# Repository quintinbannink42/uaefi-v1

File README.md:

# Ultra Affordable EFI

🟢[$175 base model rusEFI store](https://www.shop.rusefi.com/shop/p/uaefi-ultra-affordable-efi)🟢

## Community Support

🔴Community support ONLY 🔴 https://www.facebook.com/groups/rusEfi 🔴 [Discord](https://github.com/rusefi/rusefi/wiki/Discord)🔴

## SUPERSEAL 60 harness (fork)

This fork uses one TE SUPERSEAL 1.0 60-position header, **6437288-5**, on the left edge (J30 at 28.2, 138, rotation 90°, pin 1 at the south end). The dual AMPSEAL 35 headers and the 2.54 mm 2×02 sockets are removed. Ignition is logic-level smart coils only; the onboard ISL9V3040 IGBTs Q7–Q12 stay off the board. Outline is 125 × 100 mm (x 25–150, y 60–160). The old socket pin-name legend is gone; J30 keeps a silkscreen “1” on pin 1. See [docs/superseal-60-pinout.md](docs/superseal-60-pinout.md) and [docs/superseal-60-order.md](docs/superseal-60-order.md).

## Technical Details

Open Source KiCAD 7 hardware powered by [Hellen-One](https://github.com/andreika-git/hellen-one)

powerted by [rusEFI firmware](https://github.com/rusefi/rusefi)

[User Documentation](https://github.com/rusefi/rusefi/wiki/uaEFI)

## MCU options

1mg of flash is _required_.

One day we shall try https://jlcpcb.com/partdetail/Stmicroelectronics-STM32F427VIT6%2FC57097#EC or https://jlcpcb.com/partdetail/Stmicroelectronics-STM32F437VIT7%2FC1338578#EC

## rusEFI Store

https://www.shop.rusefi.com/shop/p/uaefi-ultra-affordable-efi

## HOWTO JLCPCB

You would need three files from ``boards/uaefi-a/board`` folder to place your JLCPB Assembly order: gerber.zip BOM-JLC.csv and CPL.csv

### Q: Something wrong with BOM?

A: Nope, that's normal nothing to worry about click 'Continue'.

### Q: how do I get more RAM for Lua?

A: fabricate with STM32F42xVI firmware would defect extra RAM and give you extra Lua. Once your script does not fit into STM32F42xVI it's F7 time or help us leverage F413.

### Q: I've place an order with JLCPCB and I see scary looking wrong orientation?

A: that's expected. See [boards/uaefi-c/board](boards/uaefi-c/board) ``Original*.png`` files and ``Produce*.png`` after JLCPCB manual review process.

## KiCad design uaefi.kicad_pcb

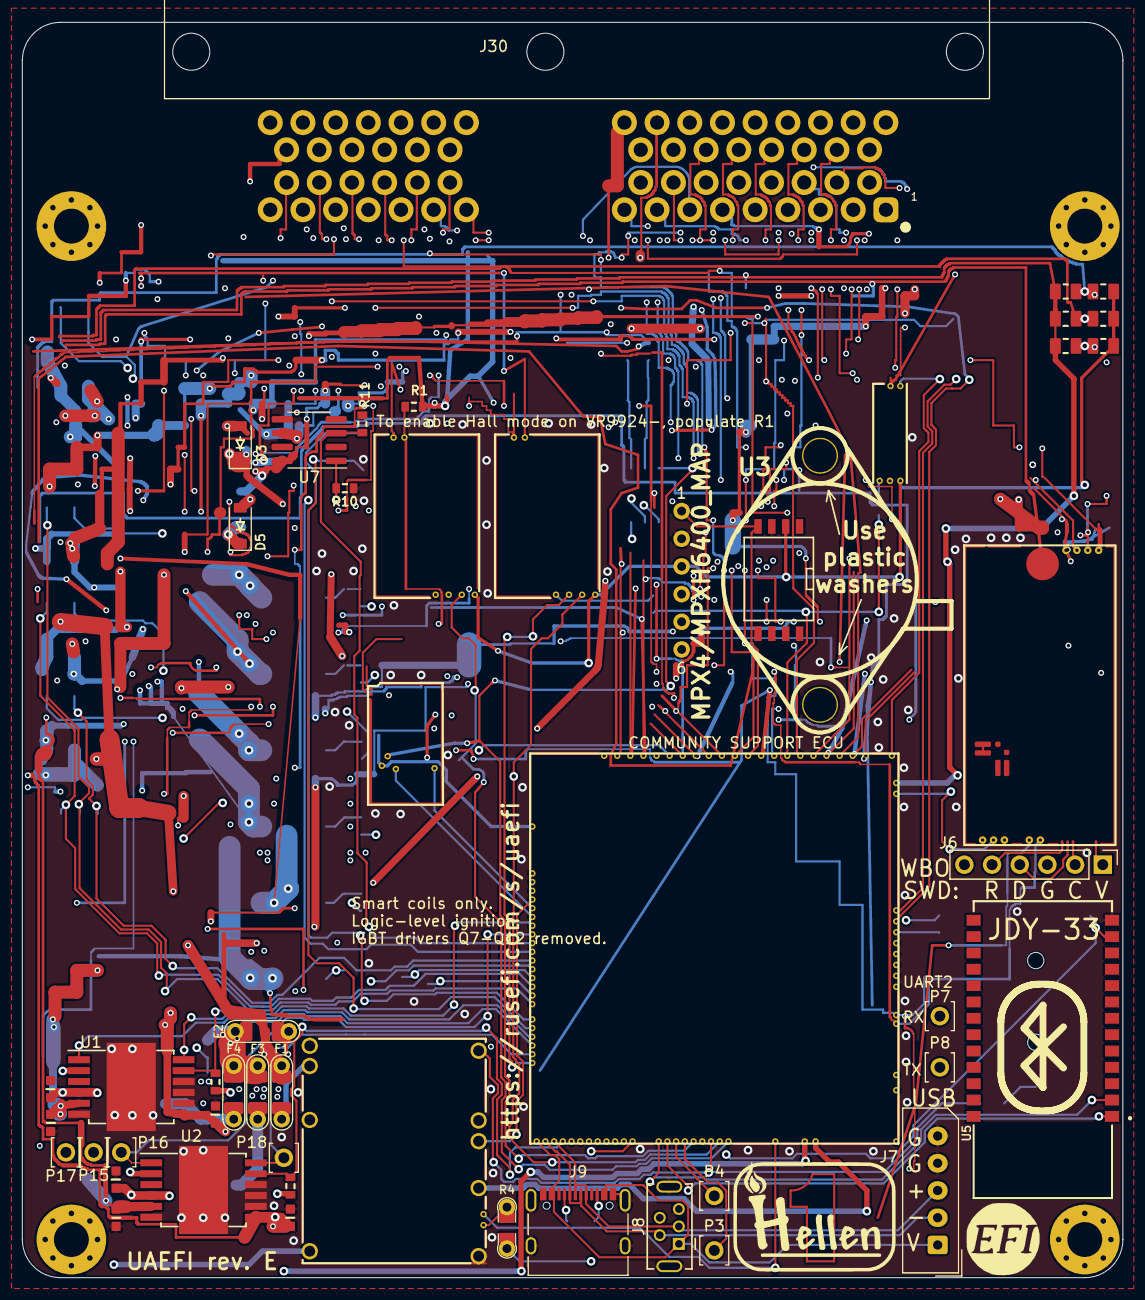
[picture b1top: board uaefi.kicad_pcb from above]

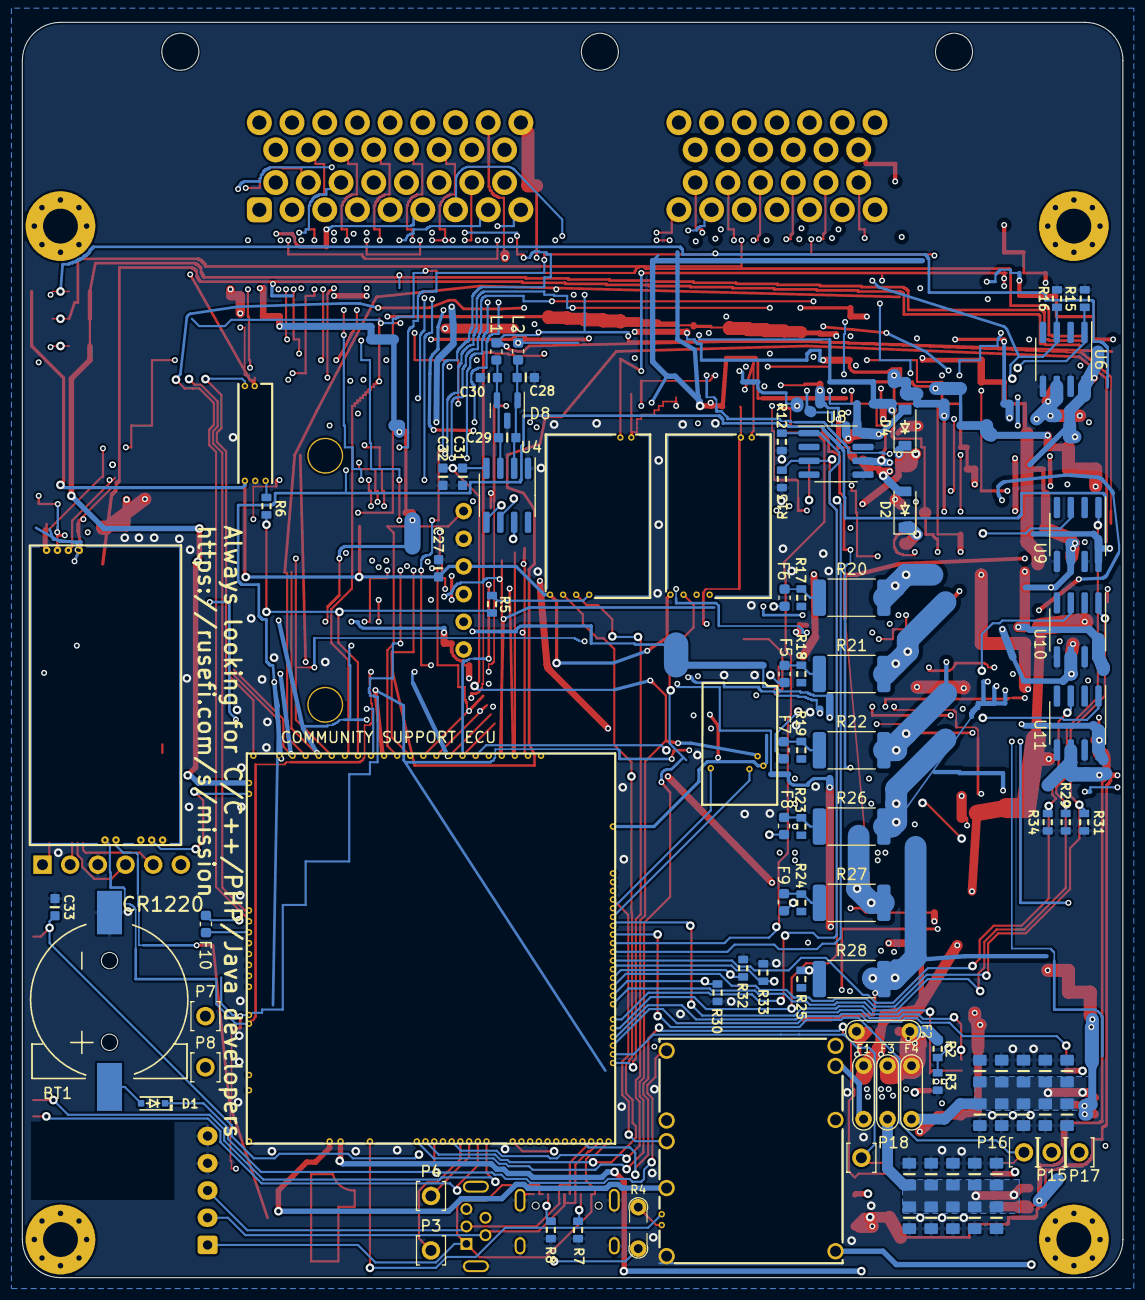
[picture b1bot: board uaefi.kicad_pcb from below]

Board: 4 copper layers, 101.0 x 115.2 mm, 129 parts (74 on the bottom side), 132 nets.

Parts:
BT1: CR1220; CR1220-2
C1, C2, C3, C4, C5, C6, C7, C8, C9, C10, C14, C15, C16, C17, C18, C19, C20, C21, C22, C23: 10u; C0805
C11, C24, C27, C29, C31, C33: 100n; C0603
C12, C13, C25, C26, C28, C30: 10n; C0603
C32: 1u; C0603
D1: 1N4148WS; SOD-323
D2, D3, D4, D5: B5819W; SOD-123
D8: NUP2105L; SOT-23
F1, F2, F3, F4: 12H1500D; PAD-1206-PAD
F5, F6, F7, F8, F9, F10: 50mA; Fuse_0603_1608Metric
G1: RUSEFI_LOGO; rusefi_logo
G2: LOGO
H1, H2, H3, H4: M3; MountingHole_3.2mm_M3_Pad_Via
J6: Conn_01x06; PinHeader_1x06_P2.54mm_Vertical
J7: Conn_01x05_Male; Molex_SPOX_5267-05A_1x05_P2.50mm_Vertical
J8: USB_B_Mini; USB-MINI-B-VERTICAL
J9: USB_C
J30: 6437288-5; TE_6437288-5_SuperSeal_60_RA
L1, L2: 470R@100MHz; L_0603_1608Metric
M1: Module-power_12and5V-0.3; power_12and5V
M2: Module-knock-0.2; knock
M3: Module-vr-discrete-0.5; vr-discrete
M4: Module-vr-max9924-0.1; vr-max9924
M5: Module-wbo-0.5; wbo
M6: Module:mega-mcu100/0.3; mega-mcu100
M7: Module-can-0.1; can
P3, P4, P7, P8, P15, P16, P17, P18: Pad; PAD-TH
R1, R9, R10, R11, R12, R13, R14, R15, R16, R29, R30, R31, R32, R33, R34: 4.7k; R0603
R2: 33k; R0603
R3: 6.8k; R0603
R4: Jumper-Pad-Pad; PAD-0805-PAD
R5, R6: 0; R0603
R7, R8: 5.6k; R0603
R17, R18, R19, R23, R24, R25: 22; R0603
R20, R21, R22, R26, R27, R28: 0; R_2512_6332Metric
R35, R36, R37: 10k; R0805
R38, R39, R40: DNP; R0805
U1, U2: TLE9201SG; Infineon_PG-DSO-12-11
U3: MPX4/MPXH6400_MAP; MPX-4_MAP
U4: MAX31855KASA; SOIC-8_3.9x4.9mm_P1.27mm
U5: JDY-33
U6, U7, U8, U9, U10, U11: VNLD5160TR-E; SOIC-8_3.9x4.9mm_P1.27mm

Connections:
+3.3V: M6.N21 (V33), R9.2, R14.2, U1.2 (VSO), U2.2 (VSO)
+3.3VA: C31.2, C32.2, C33.2, M6.N15 (V33_SWITCHABLE), M7.V2 (CAN_VIO), U4.4 (V_CC), U5.12 (3V3)
+5V: M1.E4 (V5), M6.N22 (VCC)
+5VA: C27.2, M2.E1 (V5A), M3.E4 (V5_IN), M4.E4 (V5_IN), M5.W1 (V5_IN), M6.E1 (V5A_SWITCHABLE), M6.W2 (V5A_SWITCHABLE), M7.V1 (V5), R38.2, R39.2, R40.2, U3.3 (VCC)
+5VP: J30.7, M1.V4 (5VP), R1.1
+12V: F2.1, F3.1, F4.1, J30.1, R2.2
+12V_RAW: D2.1 (K), D3.1 (K), D4.1 (K), D5.1 (K), F2.2, J30.2, M1.V1 (V12_PERM), M1.V3 (V12_RAW)
/12V_KEY: F1.1, J30.3
/ADC3: M6.S15 (IN_KNOCK_(PA2)), R5.2, R6.2
/CAN+: J30.9, M5.W4 (CANH), M6.W11 (CANH)
/CAN-: J30.35, M5.W3 (CANL), M6.W12 (CANL)
/DC1_DIR: M6.E21 (OUT_PWM4_(PC8)), P15.1, U1.1 (DIR)
/DC1_DIS: M6.E8 (SPI2_MISO_(PB14)), R9.1, U1.11 (DIS)
/DC1_PWM: M6.E20 (OUT_PWM3_(PC7)), P17.1, U1.12 (PWM)
/DC2_DIR: M6.E9 (SPI2_MOSI_(PB15)), P16.1, U2.1 (DIR)
/DC2_DIS: M6.N4 (USBID_(PA10)), R14.1, U2.11 (DIS)
/DC2_PWM: M6.E22 (OUT_PWM5_(PC9)), P18.1, U2.12 (PWM)
/DC Driver 1/PWR: C1.2, C2.2, C3.2, C4.2, C5.2, C6.2, C7.2, C8.2, C9.2, C10.2, C11.2, F4.2, U1.4 (VS)
/DC Driver 2/PWR: C14.2, C15.2, C16.2, C17.2, C18.2, C19.2, C20.2, C21.2, C22.2, C23.2, C24.2, F3.2, U2.4 (VS)
/EGT+: J30.36, L1.1
/EGT-: J30.37, L2.1
/EGT/SPI_CS: M6.N9 (SPI3_CS_(PA15)), U4.6 (~CS)
/IGN1: F6.2, M6.W10 (IGN1_(PC13))
/IGN2: F5.2, M6.W9 (IGN2_(PE5))
/IGN3: F7.2, M6.W8 (IGN3_(PE4))
/IGN4: F8.2, M6.W7 (IGN4_(PE3))
/IGN5: F9.2, M6.W6 (IGN5_(PE2))
/IGN6: F10.2, M6.W5 (IGN6_(PB8))
/INJ1: M6.E17 (OUT_INJ1_(PD3)), R29.2, U9.1 (IN1)
/INJ2: M6.E16 (OUT_INJ2_(PA9)), R30.2, U9.3 (IN2)
/INJ3: M6.E15 (OUT_INJ3_(PD11)), R31.2, U10.1 (IN1)
/INJ4: M6.E14 (OUT_INJ4_(PD10)), R32.2, U10.3 (IN2)
/INJ5: M6.E13 (OUT_INJ5_(PD2)), R33.2, U11.1 (IN1)
/INJ6: M6.E12 (OUT_INJ6_(PA8)), R34.2, U11.3 (IN2)
/INTERNAL_MAP: M6.S12 (IN_MAP2_(PC1)), U3.1 (VOUT)
/IN_AUX1: J30.23, M6.S11 (IN_O2S_/_CAN_WAKEUP_(PA0))
/IN_AUX2: J30.24, M6.S10 (IN_O2S2_(PA1))
/IN_AUX3: J30.25, M6.S7 (IN_AUX3_(PA7))
/IN_BUTTON1: J30.42, M6.S14 (IN_CRANK_(PB1)), R35.2, R38.1
/IN_BUTTON2: J30.43, M6.S16 (IN_CAM_(PA6)), R36.2, R39.1
/IN_BUTTON3: J30.44, M6.S1 (IN_D4_(PE15)), R37.2, R40.1
/IN_CLT: J30.20, M6.S21 (IN_CLT_(PC2))
/IN_FLEX: J30.21, M6.S17 (IN_VSS_(PE11))
/IN_HALL1: J30.45, M6.S4 (IN_D1_(PE12))
/IN_HALL2: J30.46, M6.S3 (IN_D2_(PE13))
/IN_HALL3: J30.47, M6.S2 (IN_D3_(PE14))
/IN_IAT: J30.19, M6.S20 (IN_IAT_(PC3))
/IN_KNOCK: M2.E3 (OUT_KNOCK), R6.1
/IN_KNOCK_RAW: J30.22, M2.W1 (IN_KNOCK)
/IN_MAP: J30.14, M6.S13 (IN_MAP1_(PC0))
/IN_PPS1: J30.17, M6.S19 (IN_PPS_(PA3))
/IN_PPS2: J30.18, M6.S8 (IN_AUX2_(PC4/PE9))
/IN_TPS1: J30.15, M6.S18 (IN_TPS_(PA4))
/IN_TPS2: J30.16, M6.S9 (IN_AUX1_(PB0))
/IN_VIGN: F1.2, M1.V2 (IN_VIGN)
/IN_VMAIN: M6.S6 (IN_AUX4_(PC5)), R2.1, R3.2
/LS1: M6.E11 (OUT_INJ7_(PD15)), R10.2, U7.1 (IN1)
/LS2: M6.E10 (OUT_INJ8_(PD12)), R11.2, U7.3 (IN2)
/LS3: M6.E18 (OUT_PWM1_(PD13)), R12.2, U8.1 (IN1)
/LS4: M6.E19 (OUT_PWM2_(PC6)), R13.2, U8.3 (IN2)
/LS_HOT1: M6.W4 (IGN7_(PB9)), R16.1, U6.3 (IN2)
/LS_HOT2: M6.W3 (IGN8_(PE6)), R15.1, U6.1 (IN1)
/MISO3: M6.N11 (SPI3_MISO_(PC11)), U4.7 (SO)
/OUT_DC1+: C13.2, J30.32, U1.7 (OUT2)
/OUT_DC1-: C12.2, J30.33, U1.5 (OUT1)
/OUT_DC2+: C26.2, J30.34, U2.7 (OUT2)
/OUT_DC2-: C25.2, J30.54, U2.5 (OUT1)
/OUT_IGN1: J30.48, R20.2
/OUT_IGN2: J30.49, R21.2
/OUT_IGN3: J30.50, R22.2
/OUT_IGN4: J30.51, R26.2
/OUT_IGN5: J30.52, R27.2
/OUT_IGN6: J30.53, R28.2
/OUT_INJ1: J30.26, U9.8 (D1)
/OUT_INJ2: J30.27, U9.6 (D2)
/OUT_INJ3: J30.28, U10.8 (D1)
/OUT_INJ4: J30.29, U10.6 (D2)
/OUT_INJ5: J30.30, U11.8 (D1)
/OUT_INJ6: J30.31, U11.6 (D2)
/OUT_LS1: D2.2 (A), J30.55, U7.8 (D1)
/OUT_LS2: D3.2 (A), J30.56, U7.6 (D2)
/OUT_LS3: D4.2 (A), J30.57, U8.8 (D1)
/OUT_LS4: D5.2 (A), J30.58, U8.6 (D2)
/OUT_LS_HOT1: J30.59, U6.6 (D2)
/OUT_LS_HOT2: J30.60, U6.8 (D1)
/PG_5VP: M6.N12 (SPI3_MOSI_(PC12)), R4.2
/PWR_EN: M1.E5 (EN_5VP), M6.N20 (OUT_PWR_EN_(PE10))
/SCK3: M6.N10 (SPI3_SCK_(PC10)), U4.5 (SCK)
/USB+: J7.3, J8.3 (D+), J9.A6 (D+), J9.B6 (D+), M6.N3 (USBP_(PA12))
/USB-: J7.2, J8.2 (D-), J9.A7 (D-), J9.B7 (D-), M6.N2 (USBM_(PA11))
/VBAT: D1.1 (K), M1.E1 (VBAT), M6.N17 (VBAT)
/VBUS: J7.1, J8.1 (VBUS), J9.A4 (VBUS), J9.A9 (VBUS), J9.B4 (VBUS), J9.B9 (VBUS), M6.N1 (VBUS)
/VIGN: M1.E3 (VIGN), M6.E5 (IN_VIGN_(PA5))
/VREF1: M2.W2 (VREF), M6.S22 (VREF1)
/VR_DISCRETE: M3.E3 (OUT), M6.N18 (UART8_RX_(PE0))
/VR_DISCRETE+: J30.40, M3.W2 (VR+)
/VR_DISCRETE-: J30.41, M3.W1 (VR-)
/VR_DISCRETE_A: M3.E2 (OUT_A), R5.1
/VR_DISCRETE_THR: M3.E1 (Thresh_IN), M6.E23 (OUT_PWM6_(PD14))
/VR_MAX9924: M4.E3 (OUT), M6.N19 (UART8_TX_(PE1))
/VR_MAX9924+: J30.38, M4.W2 (VR+)
/VR_MAX9924-: J30.39, M4.W1 (VR-), R1.2
/WBO_Heater: J30.6, M5.E5 (LSU_H+)
/WBO_Ip: J30.10, M5.E3 (LSU_Ip)
/WBO_Rtrim: J30.13, M5.E4 (LSU_Rtrim)
/WBO_Un: J30.11, M5.E1 (LSU_Un)
/WBO_Vm: J30.12, M5.E2 (LSU_Vm)
GND: BT1.2 (-), C1.1, C2.1, C3.1, C4.1, C5.1, C6.1, C7.1, C8.1, C9.1, C10.1, C11.1, C12.1, C13.1, C14.1, C15.1, C16.1, C17.1, C18.1, C19.1, C20.1, C21.1, C22.1, C23.1, C24.1, C25.1, C26.1, C27.1, C28.1, C30.1, C31.1, C32.1, C33.1, D8.3 (A), J6.3, J7.4, J7.5, J8.5 (GND), J8.6 (Shield), J9.A1 (GND), J9.A12 (GND), J9.B1 (GND), J9.B12 (GND), J9.S1 (SHIELD), J30.4, J30.5, M1.S1 (GND), M2.E2 (GND), M3.G (GND), M4.G (GND), M5.E6 (LSU_H-), M5.G (GND), M6.G (GND), M7.E1 (GND), R3.1, R7.1, R8.1, R10.1, R11.1, R12.1, R13.1, R15.2, R16.2, R29.1, R30.1, R31.1, R32.1, R33.1, R34.1, U1.6 (GND), U1.8 (SI), U1.9 (CSN), U1.10 (SCK), U1.13 (GND), U2.6 (GND), U2.8 (SI), U2.9 (CSN), U2.10 (SCK), U2.13 (GND), U3.2 (GND), U4.1 (GND), U5.13 (GND), U6.5 (S2), U6.7 (S1), U7.5 (S2), U7.7 (S1), U8.5 (S2), U8.7 (S1), U9.5 (S2), U9.7 (S1), U10.5 (S2), U10.7 (S1), U11.5 (S2), U11.7 (S1)
GNDA: J30.8, M6.W1 (GNDA), R35.1, R36.1, R37.1
unnamed: BT1.1 (+), D1.2 (A)
unnamed: F5.1, R18.2, R21.1
unnamed: F6.1, R17.2, R20.1
unnamed: F7.1, R19.2, R22.1
unnamed: F8.1, R23.2, R26.1
unnamed: F9.1, R24.2, R27.1
unnamed: F10.1, R25.2, R28.1
unnamed: J6.1, M5.W8 (V33_OUT)
unnamed: J6.2, M5.W7 (SWCLK)
unnamed: J6.4, M5.W6 (SWDIO)
unnamed: J6.5, M5.W5 (nReset)
unnamed: J9.A5 (CC1), R7.2
unnamed: J9.B5 (CC2), R8.2
unnamed: M1.E6 (PG_5VP), R4.1
unnamed: M5.J1 (SEL1), M5.J_GND1 (PULL_DOWN1)
unnamed: M6.N14a (LED_GREEN), P4.1
unnamed: M6.N14b (LED_YELLOW), P3.1
unnamed: M6.E6 (SPI2_CS_/_CAN2_RX_(PB12)), M7.V6 (CAN_RX)
unnamed: M6.E7 (SPI2_SCK_/_CAN2_TX_(PB13)), M7.V5 (CAN_TX)
unnamed: M6.N14 (UART2_RX_(PD6)), P7.1, U5.1 (TXD)
unnamed: M6.N13 (UART2_TX_(PD5)), P8.1, U5.2 (RXD)
unnamed: C29.2, C30.2, D8.2 (K), L1.2, U4.3 (T+)
unnamed: C28.2, C29.1, D8.1 (K), L2.2, U4.2 (T-)
